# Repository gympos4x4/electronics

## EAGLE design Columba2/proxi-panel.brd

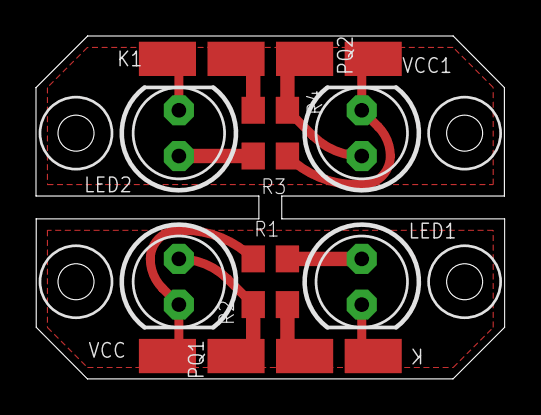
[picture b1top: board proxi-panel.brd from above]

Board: 2 copper layers, 26.0 x 19.1 mm, 16 parts (0 on the bottom side), 10 nets.

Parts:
GND, GND1: SMD1,27-2,54
K, K1: SMD1,27-2,54
LED1, LED2: LED5MM
OUT, OUT1: SMD1,27-2,54
PQ1, PQ2: PHOTOTRANSISTOR-5MM; LED5MM
R1, R3: 300R; R0805
R2, R4: 1k; R0805
VCC, VCC1: SMD1,27-2,54

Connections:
GND: GND.1, R2.1
GND1: GND1.1, R4.1
unnamed: K.1, LED1.K
unnamed: LED2.A, R3.2
unnamed: K1.1, LED2.K
unnamed: LED1.A, R1.2
OUT: OUT.1, PQ1.A, R2.2
OUT1: OUT1.1, PQ2.A, R4.2
VCC: PQ1.K, R1.1, VCC.1
VCC1: PQ2.K, R3.1, VCC1.1
